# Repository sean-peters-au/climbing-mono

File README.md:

Betaboard is an over-engineered, over-the-top climbing board app. It is very in progress.

The goal is to
- Track 3 axes forces applied over climbing holds, and skeletal kinematics of the climber
- 3D visualisation of the forces and climber on the board
- Biomechanics approximations from this time-series data

<br>
<br>
<br>

## Installing

TODO

# Getting Started

TODO

## Usage

TODO

## Contributing

TODO

## Changelog

TODO

## Acknowledgments

TODO

## License

TODO

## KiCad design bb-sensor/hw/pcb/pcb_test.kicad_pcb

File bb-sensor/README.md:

# BetaBoard Sensor

- Load Cell Housing STL(`sensor_housing.py`)
- Sensor PCB (`sensor_pcb_footprint.py`)

## Environment Setup

### 1. Install Miniforge (conda for Apple Silicon)

```bash
    brew install miniforge
```

### 2. Create and activate environment

```bash
    # Create environment
    conda create -n bb-sensor python=3.10

    # Activate environment
    conda activate bb-sensor
```

### 3. Install dependencies

```bash
    # Install CAD and PCB design tools
    conda install --file conda-requirements.txt
    pip install -r requirements.txt

    # Install KiCad
    brew install --cask kicad

    # Configure KiCad environment (run after activating conda environment)
    conda env config vars set KICAD_SYMBOL_DIR="/Applications/KiCad/KiCad.app/Contents/SharedSupport/symbols"
    conda env config vars set KICAD8_SYMBOL_DIR="/Applications/KiCad/KiCad.app/Contents/SharedSupport/symbols"

    # Reactivate environment for changes to take effect
    conda deactivate
    conda activate bb-sensor
```

## Usage

### Generate 3D Housing

```bash
    python scripts/sensor_housing.py
```

This will create `housing_unit.stl` in the current directory.

### Generate PCB Netlist

```bash
    python scripts/sensor_pcb_footprint.py
```

This will create `climbing_hold_sensors.net` which can be imported into KiCad for schematic and PCB layout.
```

/Applications/Kicad/Kicad.app/Contents/Frameworks/Python.framework/Versions/Current/bin/python3 scripts/pcb_test.py

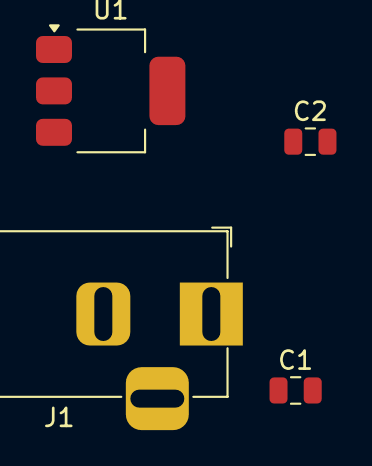
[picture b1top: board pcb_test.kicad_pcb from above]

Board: 2 copper layers, 4 parts (0 on the bottom side), 3 nets, no tracks yet.

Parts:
C1, C2: 10uF; C_0805_2012Metric
J1: Barrel_Jack; BarrelJack_Horizontal
U1: LD1117S33TR_SOT223; SOT-223-3_TabPin2

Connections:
3V3: C2.1, U1.2
GND: C1.2, C2.2, J1.2, U1.1
VIN_5V: C1.1, J1.1, U1.3

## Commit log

2024-09-21 large starting commit for all my climbing tools
2024-09-24 working
2024-09-26 actually working with my home wall
2024-09-26 use .env for secrets
2024-09-26 app much more pretty
2024-09-29 imaging service + sensors + individual hold id (all wip)
2024-10-19 imaging service + sensors + individual hold id (all wip) cont.
2024-10-22 imaging service + sensors + individual hold id working
2024-10-22 bunch of UX improvements and a start on analysis endpoint in backend
2024-10-22 more ux improvements
2024-10-23 initial analysis working
2024-10-24 hold overlay refactor
2024-10-24 lots of ux improvements
2024-10-24 use hold numbers not ids for analysis
2024-10-26 improving analysis section
2024-10-26 beta & analysis section is now nested accordians
2024-10-29 analysis visualistions working
2024-10-29 refactor to use dao pattern
2024-10-30 working again after migration to postgres
2024-10-30 update gitignore
2024-10-31 add fallbacks for holds that aren't segmented by sam
2024-11-06 add pi camera service app
2024-11-06 add betaboard-camera as a service to the backend
2024-11-06 add quick climber kinematics poc
2024-11-06 move hold-metrics to poc
2024-11-06 update hold-metrics readme
2024-11-19 camera support wip
2024-11-19 editing routes works
2024-11-21 board photogrammetry working v1
2024-11-21 working board-photogrammetry with colour and react viewer
2024-11-26 video feed working
2024-11-26 video recording and feed working in frontend
2024-11-26 rename top level dirs
2024-11-26 kinematics wip + slowly improving docs
2024-11-26 fix readme
2024-11-26 readme
2024-11-27 first end to end half working kinematics
2024-11-28 bb-camera improvements
2024-11-28 giving up on h264 video feed for now
2024-11-28 add camera service to frontend
2024-11-29 recordings play in UI
2024-11-29 refactor camera app
2024-11-29 fixing various small bugs
2024-11-30 hold highlights are now borders only
2024-12-28 bb sensor hw wip
2025-02-04 visual panel refactor
2025-03-19 improvements to hold load cell poc
